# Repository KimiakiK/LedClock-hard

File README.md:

# LED Clock
[Software](https://github.com/KimiakiK/LedClock-soft)

# Features
- LED 60個で時刻を表示

# Major Components  
- STM32F303K8
- 16ch LEDドライバ PCA9635PW
- スイッチ付きロータリーエンコーダ

## PCB
- V1.1

- V1.0

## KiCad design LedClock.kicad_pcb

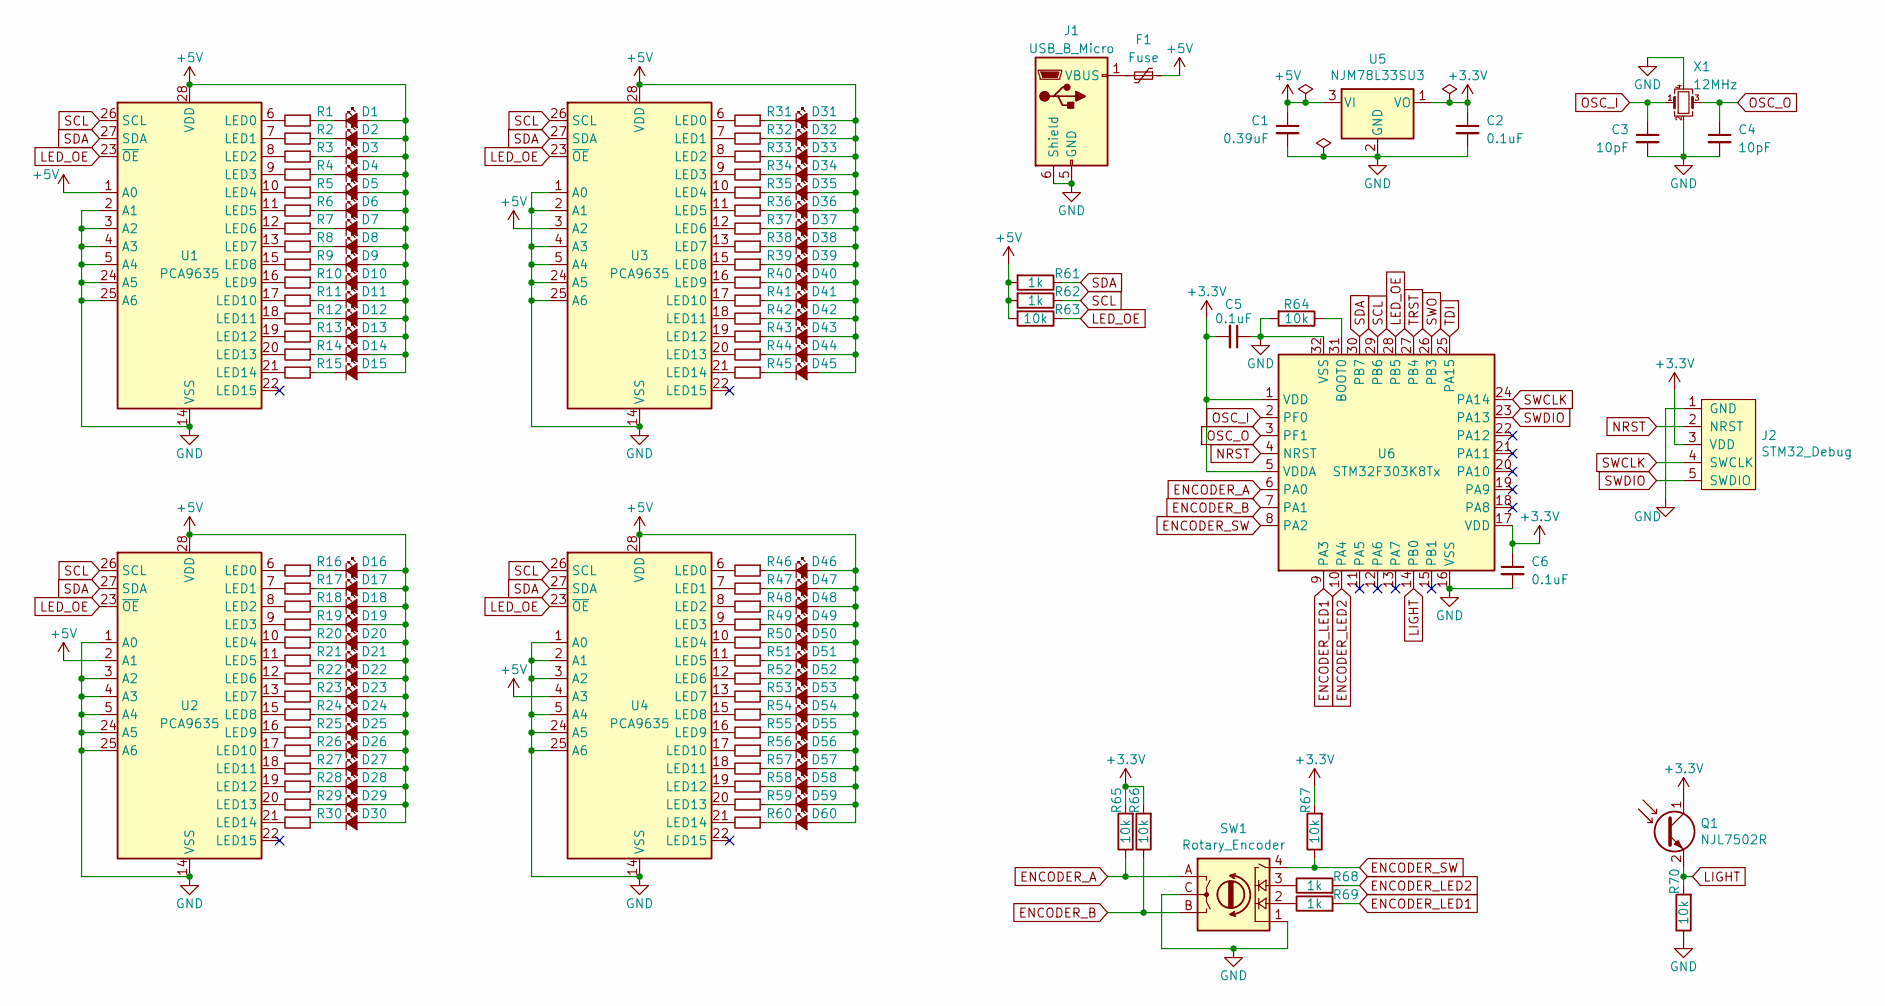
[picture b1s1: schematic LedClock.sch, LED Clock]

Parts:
C1: 0.39uF; C_0603_1608Metric_Pad1.05x0.95mm_HandSolder
C2, C5, C6: 0.1uF; C_0603_1608Metric_Pad1.05x0.95mm_HandSolder
C3, C4: 10pF; C_0402_1005Metric
D1, D2, D3, D4, D5, D6, D7, D8, D9, D10, D11, D12, D13, D14, D15, D16, D17, D18, D19, D20, D21, D22, D23, D24, D25, D26, D27, D28, D29, D30, D31, D32, D33, D34, D35, D36, D37, D38, D39, D40, D41, D42, D43, D44, D45, D46, D47, D48, D49, D50, D51, D52, D53, D54, D55, D56, D57, D58, D59, D60: LED_Small_ALT; LED_CLOCK
F1: Fuse; Fuse_1206_3216Metric_Pad1.42x1.75mm_HandSolder
J1: USB_B_Micro; USB_Micro-B_PowerOnly
J2: STM32_Debug; STM32_Debug_5pin
Q1: NJL7502R
R1, R2, R3, R4, R5, R6, R7, R8, R9, R10, R11, R12, R13, R14, R15, R16, R17, R18, R19, R20, R21, R22, R23, R24, R25, R26, R27, R28, R29, R30, R31, R32, R33, R34, R35, R36, R37, R38, R39, R40, R41, R42, R43, R44, R45, R46, R47, R48, R49, R50, R51, R52, R53, R54, R55, R56, R57, R58, R59, R60: R; R_0603_1608Metric_Pad1.05x0.95mm_HandSolder
R61, R62, R68, R69: 1k; R_0603_1608Metric_Pad1.05x0.95mm_HandSolder
R63, R64, R65, R66, R67, R70: 10k; R_0603_1608Metric_Pad1.05x0.95mm_HandSolder
SW1: Rotary_Encoder; Rotary_Encoder_SW_2LED
U1, U2, U3, U4: PCA9635; TSSOP-28_4.4x9.7mm_P0.65mm
U5: NJM78L33SU3; SOT-89-3_Handsoldering
U6: STM32F303K8Tx; LQFP-32_7x7mm_P0.8mm_FusionPCB
X1: 12MHz; Crystal_SMD_3225-4Pin_3.2x2.5mm_HandSoldering

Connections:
+3V3: C2.1, C5.2, C6.1, J2.3 (VDD), Q1.1 (C), R65.2, R66.2, R67.2, U5.1 (VO), U6.1 (VDD), U6.5 (VDDA), U6.17 (VDD)
+5V: C1.1, D1.2 (A), D2.2 (A), D3.2 (A), D4.2 (A), D5.2 (A), D6.2 (A), D7.2 (A), D8.2 (A), D9.2 (A), D10.2 (A), D11.2 (A), D12.2 (A), D13.2 (A), D14.2 (A), D15.2 (A), D16.2 (A), D17.2 (A), D18.2 (A), D19.2 (A), D20.2 (A), D21.2 (A), D22.2 (A), D23.2 (A), D24.2 (A), D25.2 (A), D26.2 (A), D27.2 (A), D28.2 (A), D29.2 (A), D30.2 (A), D31.2 (A), D32.2 (A), D33.2 (A), D34.2 (A), D35.2 (A), D36.2 (A), D37.2 (A), D38.2 (A), D39.2 (A), D40.2 (A), D41.2 (A), D42.2 (A), D43.2 (A), D44.2 (A), D45.2 (A), D46.2 (A), D47.2 (A), D48.2 (A), D49.2 (A), D50.2 (A), D51.2 (A), D52.2 (A), D53.2 (A), D54.2 (A), D55.2 (A), D56.2 (A), D57.2 (A), D58.2 (A), D59.2 (A), D60.2 (A), F1.1, R61.2, R62.2, R63.2, U1.1 (A0), U1.28 (VDD), U2.2 (A1), U2.28 (VDD), U3.3 (A2), U3.28 (VDD), U4.4 (A3), U4.28 (VDD), U5.3 (VI)
ENCODER_A: R65.1, SW1.A, U6.6 (PA0)
ENCODER_B: R66.1, SW1.B, U6.7 (PA1)
ENCODER_LED1: R69.2, U6.9 (PA3)
ENCODER_LED2: R68.2, U6.10 (PA4)
ENCODER_SW: R67.1, SW1.4, U6.8 (PA2)
GND: C1.2, C2.2, C3.2, C4.2, C5.1, C6.2, J1.5 (GND), J1.6 (Shield), J2.1 (GND), R64.2, R70.1, SW1.1, SW1.C, U1.2 (A1), U1.3 (A2), U1.4 (A3), U1.5 (A4), U1.14 (VSS), U1.24 (A5), U1.25 (A6), U2.1 (A0), U2.3 (A2), U2.4 (A3), U2.5 (A4), U2.14 (VSS), U2.24 (A5), U2.25 (A6), U3.1 (A0), U3.2 (A1), U3.4 (A3), U3.5 (A4), U3.14 (VSS), U3.24 (A5), U3.25 (A6), U4.1 (A0), U4.2 (A1), U4.3 (A2), U4.5 (A4), U4.14 (VSS), U4.24 (A5), U4.25 (A6), U5.2 (GND), U6.16 (VSS), U6.32 (VSS), X1.2, X1.4
LED_OE: R63.1, U1.23 (~OE), U2.23 (~OE), U3.23 (~OE), U4.23 (~OE), U6.28 (PB5)
LIGHT: Q1.2 (E), R70.2, U6.14 (PB0)
NRST: J2.2 (NRST), U6.4 (NRST)
unnamed: D1.1 (K), R1.1
unnamed: D2.1 (K), R2.1
unnamed: D3.1 (K), R3.1
unnamed: D4.1 (K), R4.1
unnamed: D5.1 (K), R5.1
unnamed: D6.1 (K), R6.1
unnamed: D7.1 (K), R7.1
unnamed: D8.1 (K), R8.1
unnamed: D9.1 (K), R9.1
unnamed: D10.1 (K), R10.1
unnamed: D11.1 (K), R11.1
unnamed: D12.1 (K), R12.1
unnamed: D13.1 (K), R13.1
unnamed: D14.1 (K), R14.1
unnamed: D15.1 (K), R15.1
unnamed: D16.1 (K), R16.1
unnamed: D17.1 (K), R17.1
unnamed: D18.1 (K), R18.1
unnamed: D19.1 (K), R19.1
unnamed: D20.1 (K), R20.1
unnamed: D21.1 (K), R21.1
unnamed: D22.1 (K), R22.1
unnamed: D23.1 (K), R23.1
unnamed: D24.1 (K), R24.1
unnamed: D25.1 (K), R25.1
unnamed: D26.1 (K), R26.1
unnamed: D27.1 (K), R27.1
unnamed: D28.1 (K), R28.1
unnamed: D29.1 (K), R29.1
unnamed: D30.1 (K), R30.1
unnamed: D31.1 (K), R31.1
unnamed: D32.1 (K), R32.1
unnamed: D33.1 (K), R33.1
unnamed: D34.1 (K), R34.1
unnamed: D35.1 (K), R35.1
unnamed: D36.1 (K), R36.1
unnamed: D37.1 (K), R37.1
unnamed: D38.1 (K), R38.1
unnamed: D39.1 (K), R39.1
unnamed: D40.1 (K), R40.1
unnamed: D41.1 (K), R41.1
unnamed: D42.1 (K), R42.1
unnamed: D43.1 (K), R43.1
unnamed: D44.1 (K), R44.1
unnamed: D45.1 (K), R45.1
unnamed: D46.1 (K), R46.1
unnamed: D47.1 (K), R47.1
unnamed: D48.1 (K), R48.1
unnamed: D49.1 (K), R49.1
unnamed: D50.1 (K), R50.1
unnamed: D51.1 (K), R51.1
unnamed: D52.1 (K), R52.1
unnamed: D53.1 (K), R53.1
unnamed: D54.1 (K), R54.1
unnamed: D55.1 (K), R55.1
unnamed: D56.1 (K), R56.1
unnamed: D57.1 (K), R57.1
unnamed: D58.1 (K), R58.1
unnamed: D59.1 (K), R59.1
unnamed: D60.1 (K), R60.1
unnamed: F1.2, J1.1 (VBUS)
unnamed: R1.2, U1.6 (LED0)
unnamed: R2.2, U1.7 (LED1)
unnamed: R3.2, U1.8 (LED2)
unnamed: R4.2, U1.9 (LED3)
unnamed: R5.2, U1.10 (LED4)
unnamed: R6.2, U1.11 (LED5)
unnamed: R7.2, U1.12 (LED6)
unnamed: R8.2, U1.13 (LED7)
unnamed: R9.2, U1.15 (LED8)
unnamed: R10.2, U1.16 (LED9)
unnamed: R11.2, U1.17 (LED10)
unnamed: R12.2, U1.18 (LED11)
unnamed: R13.2, U1.19 (LED12)
unnamed: R14.2, U1.20 (LED13)
unnamed: R15.2, U1.21 (LED14)
unnamed: R16.2, U2.6 (LED0)
unnamed: R17.2, U2.7 (LED1)
unnamed: R18.2, U2.8 (LED2)
unnamed: R19.2, U2.9 (LED3)
unnamed: R20.2, U2.10 (LED4)
unnamed: R21.2, U2.11 (LED5)
unnamed: R22.2, U2.12 (LED6)
unnamed: R23.2, U2.13 (LED7)
unnamed: R24.2, U2.15 (LED8)
unnamed: R25.2, U2.16 (LED9)
unnamed: R26.2, U2.17 (LED10)
unnamed: R27.2, U2.18 (LED11)
unnamed: R28.2, U2.19 (LED12)
unnamed: R29.2, U2.20 (LED13)
unnamed: R30.2, U2.21 (LED14)
unnamed: R31.2, U3.6 (LED0)
unnamed: R32.2, U3.7 (LED1)
unnamed: R33.2, U3.8 (LED2)
unnamed: R34.2, U3.9 (LED3)
unnamed: R35.2, U3.10 (LED4)
unnamed: R36.2, U3.11 (LED5)
unnamed: R37.2, U3.12 (LED6)
unnamed: R38.2, U3.13 (LED7)
unnamed: R39.2, U3.15 (LED8)
unnamed: R40.2, U3.16 (LED9)
unnamed: R41.2, U3.17 (LED10)
unnamed: R42.2, U3.18 (LED11)
unnamed: R43.2, U3.19 (LED12)
unnamed: R44.2, U3.20 (LED13)
unnamed: R45.2, U3.21 (LED14)
unnamed: R46.2, U4.6 (LED0)
unnamed: R47.2, U4.7 (LED1)
unnamed: R48.2, U4.8 (LED2)
unnamed: R49.2, U4.9 (LED3)
unnamed: R50.2, U4.10 (LED4)
unnamed: R51.2, U4.11 (LED5)
unnamed: R52.2, U4.12 (LED6)
unnamed: R53.2, U4.13 (LED7)
unnamed: R54.2, U4.15 (LED8)
unnamed: R55.2, U4.16 (LED9)
unnamed: R56.2, U4.17 (LED10)
unnamed: R57.2, U4.18 (LED11)
unnamed: R58.2, U4.19 (LED12)
unnamed: R59.2, U4.20 (LED13)
unnamed: R60.2, U4.21 (LED14)
unnamed: R64.1, U6.31 (BOOT0)
unnamed: R68.1, SW1.3
unnamed: R69.1, SW1.2
OSC_I: C3.1, U6.2 (PF0), X1.1
OSC_O: C4.1, U6.3 (PF1), X1.3
SCL: R62.1, U1.26 (SCL), U2.26 (SCL), U3.26 (SCL), U4.26 (SCL), U6.29 (PB6)
SDA: R61.1, U1.27 (SDA), U2.27 (SDA), U3.27 (SDA), U4.27 (SDA), U6.30 (PB7)
SWCLK: J2.4 (SWCLK), U6.24 (PA14)
SWDIO: J2.5 (SWDIO), U6.23 (PA13)

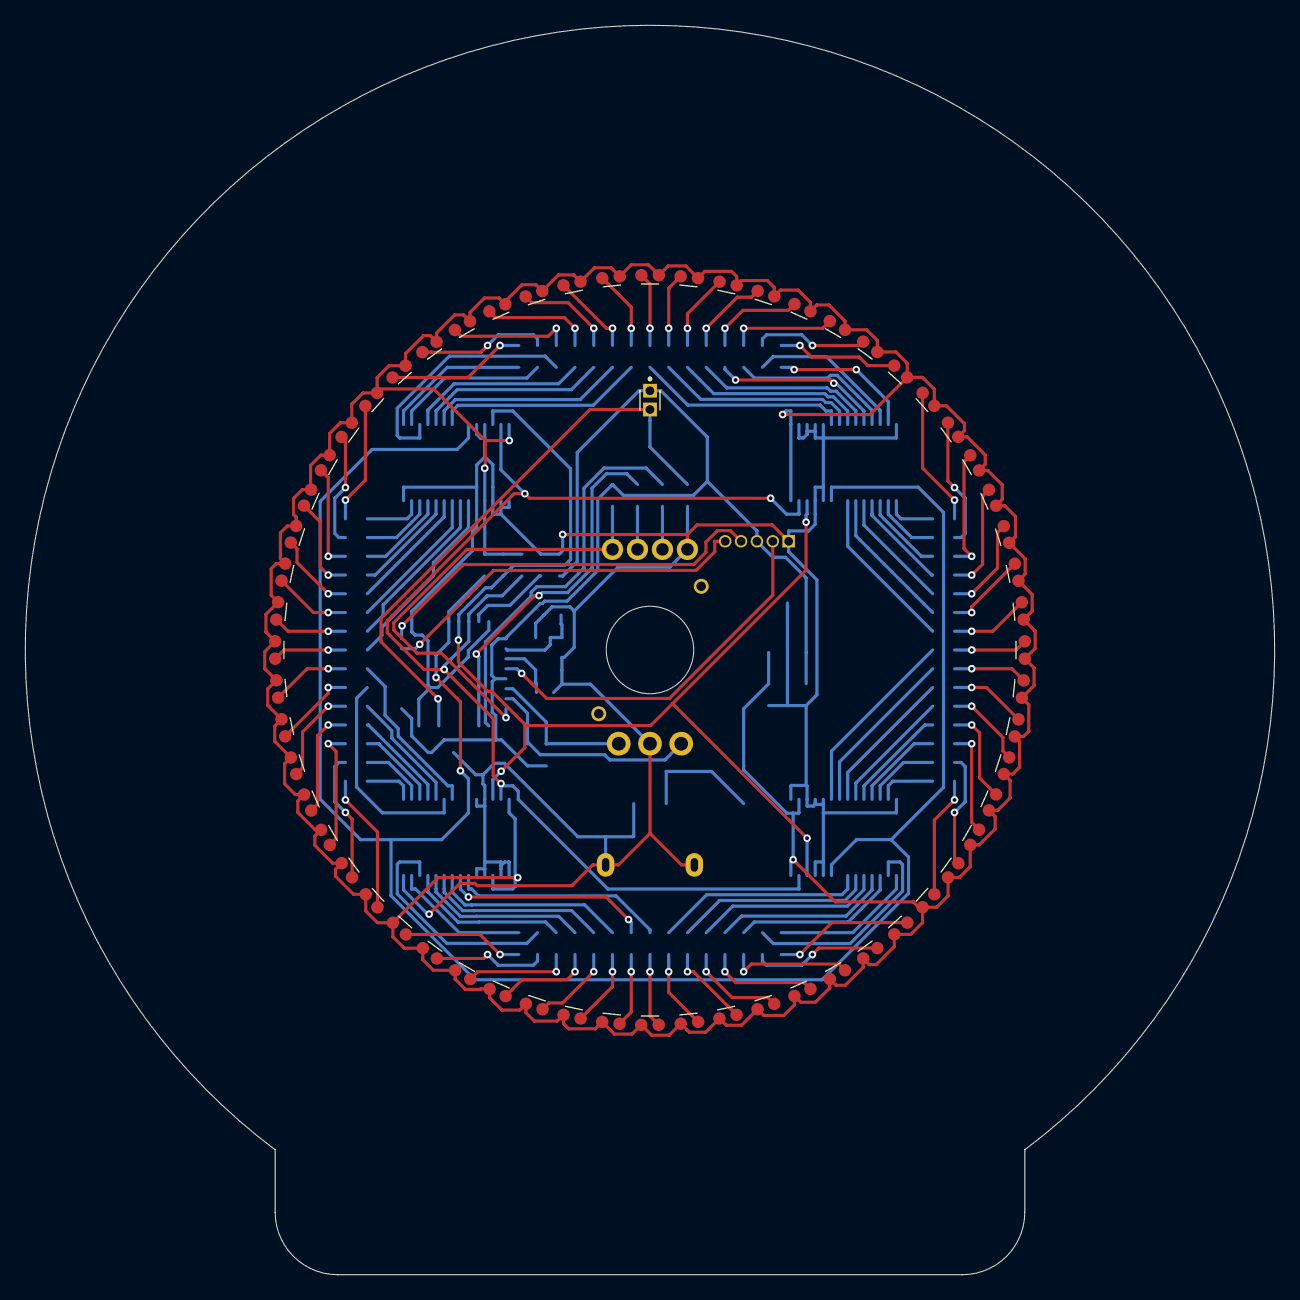
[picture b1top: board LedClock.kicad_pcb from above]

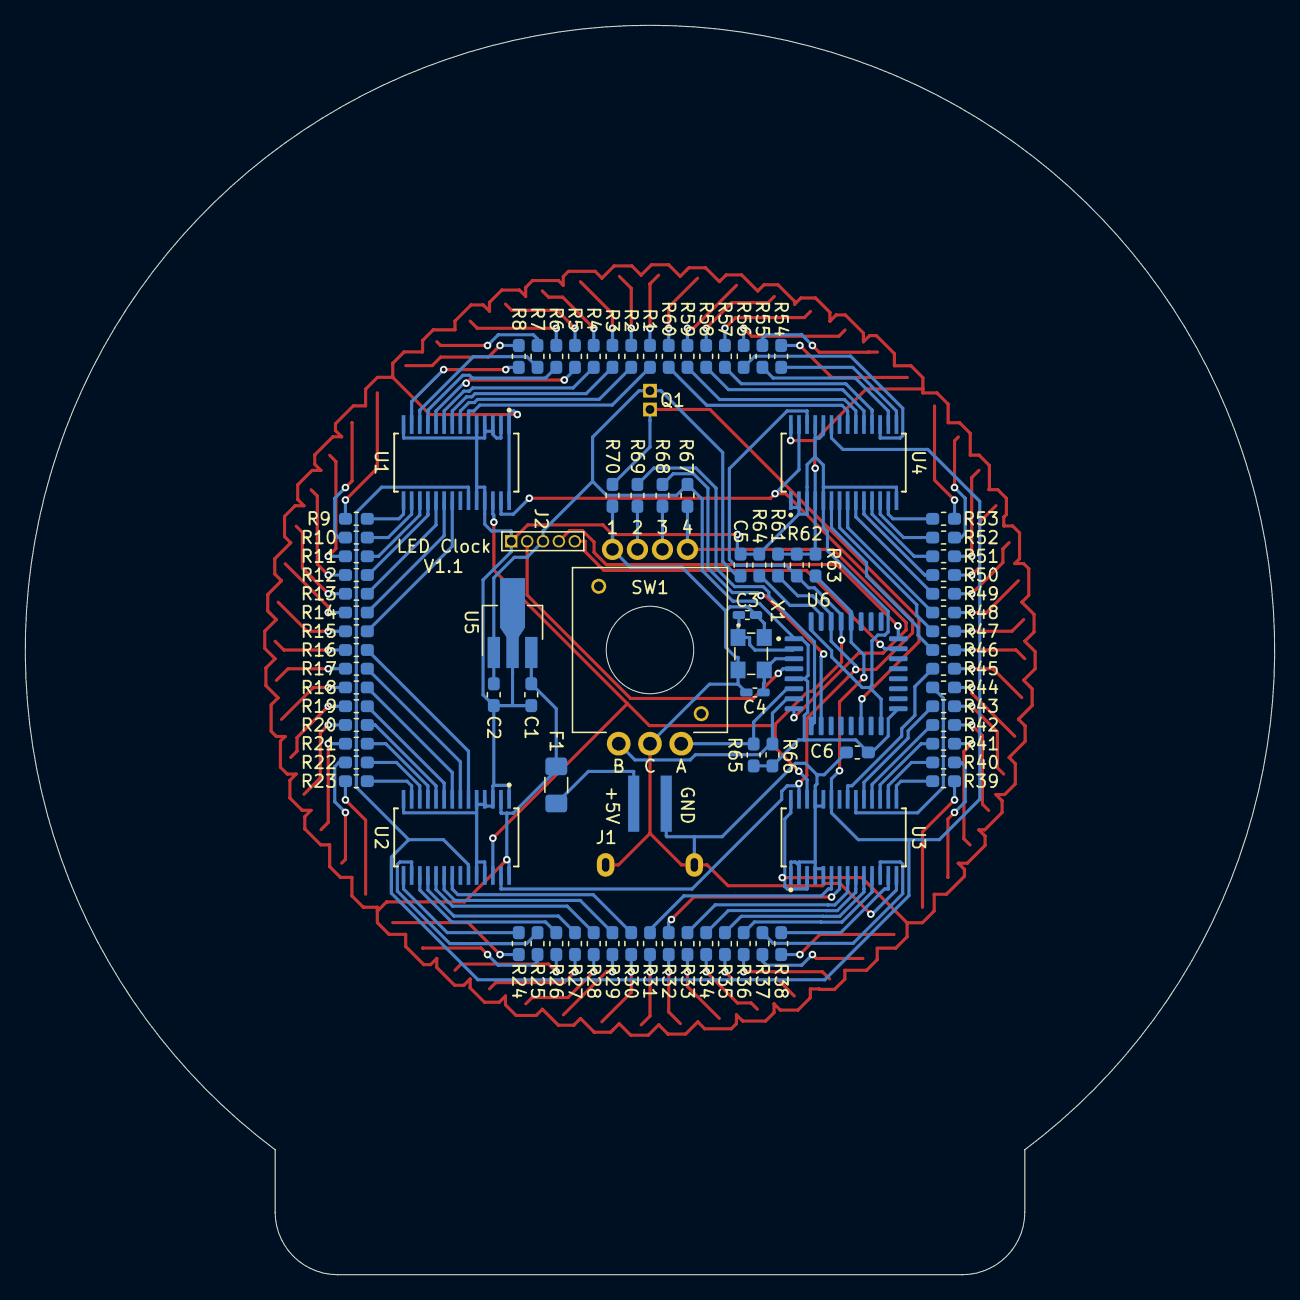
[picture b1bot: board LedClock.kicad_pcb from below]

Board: 2 copper layers, 100.0 x 100.0 mm, 148 parts (86 on the bottom side), 141 nets.

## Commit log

2021-02-10 基板 V1.0
2021-02-10 基板 V1.1
2021-04-29 Add images
